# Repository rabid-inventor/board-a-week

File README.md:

# board-a-week
Board a week project. 

Week 1: PASSIVE BLOCK XOR GATE

Attempting to design a pcb to demonstarate an XOR using Discreet silicon and passive components.
REV1 Design Completed 17/07/18

Week 2: TINYMCU

A Breakout for the Atmel/Microchip AtTiny 4/5/9/10 also suitabe for Microchip PIC10F320/322
REV1 Design Complete 24/07/18

Week 3: INTOKICAD / RABIDCHARLIE

First design using KiCAD Wish me luck. This week I ending up with two designs IntoKiCAD is unfinished it was my first steps in using KiCAD. RabidCHARLE is a complete board ready to produce, containing 12 Charlieplexed LEDs.
RabidCHARLIE REV1 Design Complete 31/07/18

Week 4: BUBBLE WATCH

In Progress!!! , base board finish upper board still work to be done 

Week 5: Lets try a new IC

A breakout board for the brand new BMA400 Accelerometer, designed using limited datasheet information. 

Design Complete 27/08/17

Week 6: Blink A Led

Entry for the Mouser / MacroFAB Blink A Led competition

License / Warranty

These source documents are Licenced as CC-BY feel free to use them just drop me a mention in future projects using them. :)
For further details see LICENCE.md

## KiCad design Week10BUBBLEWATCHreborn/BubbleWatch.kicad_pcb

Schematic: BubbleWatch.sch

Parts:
BT1, BT2: Battery_Cell; BatteryHolder_Keystone_3000_1x12mm
C1, C7: 4.7uF; C_0603_1608Metric
C2, C3: 100nF; C_0603_1608Metric
C4: 10nF; C_0603_1608Metric
C5: 1uF; C_0603_1608Metric
C6, C8: 12pF; C_0603_1608Metric
C9: 10uF; C_0603_1608Metric
J1, J2: Conn_02x02_Counter_Clockwise; PinHeader_2x02_P2.54mm_Vertical_SMD
J3: Conn_01x05; Harwin_M20-89005xx_1x05_P2.54mm_Horizontal
L1: 4.7uH; L_Taiyo-Yuden_NR-30xx
R1: 330K; R_0603_1608Metric
R2: 200k; R_0603_1608Metric
R3: 10k; R_0603_1608Metric
RN1, RN2: 220R; R_Array_Concave_4x0402
SW1, SW2, SW3, SW4: SW_Push; Panasonic_EVQPUM_EVQPUD
U1, U2: RedRetroBubbleDisplay; DIP-12_W7.62mm_SMDSocket_SmallPads
U3: STM32F030C8Tx; LQFP-48_7x7mm_P0.5mm
U4: MCP1640BCH; SOT-23-6
Y1: Crystal; Crystal_DS10_D1.0mm_L4.3mm_Horizontal_1EP_style1

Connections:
+3V3: C1.1, C2.1, C3.1, C4.1, C5.1, C9.1, J1.4, J2.4, J3.1, R1.1, R3.1, U3.1, U3.9, U3.24, U3.48, U4.5 (VOUT); also elsewhere on the board
+BATT: BT1.1, BT2.1, C7.1, J1.1, J1.2, J2.1, J2.2, L1.1, U4.3 (EN), U4.6 (VIN)
/BOOT0: U3.44
/BUTTON1: SW1.2, U3.e
/BUTTON2: SW2.2, U3.46
/BUTTON3: SW3.2, U3.45
/BUTTON4: SW4.2, U3.39
/DIS1: U1.1, U3.18
/DIS2: U1.10, U3.19
/DIS3: U1.4, U3.20
/DIS4: U1.6, U3.21
/DIS5: U2.1, U3.25
/DIS6: U2.10, U3.27
/DIS7: U2.4, U3.26
/DIS8: U2.6, U3.28
/I2C1_SCL: J3.3, U3.35
/I2C1_SDA: J3.4, U3.36
/IOSEGA: RN1.4, U3.5
/IOSEGB: RN1.3, U3.6
/IOSEGC: RN1.2, U3.10
/IOSEGD: RN1.1, U3.11
/IOSEGDP: RN2.1, U3.43
/IOSEGE: RN2.4, U3.40
/IOSEGF: RN2.3, U3.41
/IOSEGG: RN2.2, U3.42
/RESET: R3.2, U3.7; also elsewhere on the board
/RTC_XTAL_IN: C6.1, U3.3, Y1.1
/RTC_XTAL_OUT: C8.1, U3.4, Y1.2
/SEGA: RN1.7, U1.12, U2.12
/SEGB: RN1.8, U1.11, U2.11
/SEGC: RN1.6, U1.3, U2.3
/SEGD: RN2.6, U1.8, U2.8
/SEGDP: RN2.8, U1.5, U2.5
/SEGE: RN1.5, U1.2, U2.2
/SEGF: RN2.5, U1.9, U2.9
/SEGG: RN2.7, U1.7, U2.7
/SWDCLK: U3.37; also elsewhere on the board
/SWDIO: U3.34; also elsewhere on the board
GND: BT1.2, BT2.2, C1.2, C2.2, C3.2, C4.2, C5.2, C6.2, C7.2, C8.2, C9.2, J1.3, J2.3, J3.2, J3.5, R2.2, SW1.1, SW2.1, SW3.1, SW4.1, U3.8, U3.23, U3.47, U4.2 (GND); also elsewhere on the board
unnamed: L1.2, U4.1 (SW)
unnamed: R1.2, R2.1, U4.4 (VFB)
unnamed: J3.9, U3.16
unnamed: J3.10, U3.17

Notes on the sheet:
Top/Bottom Board interconnect
Programming header
Decoupleing

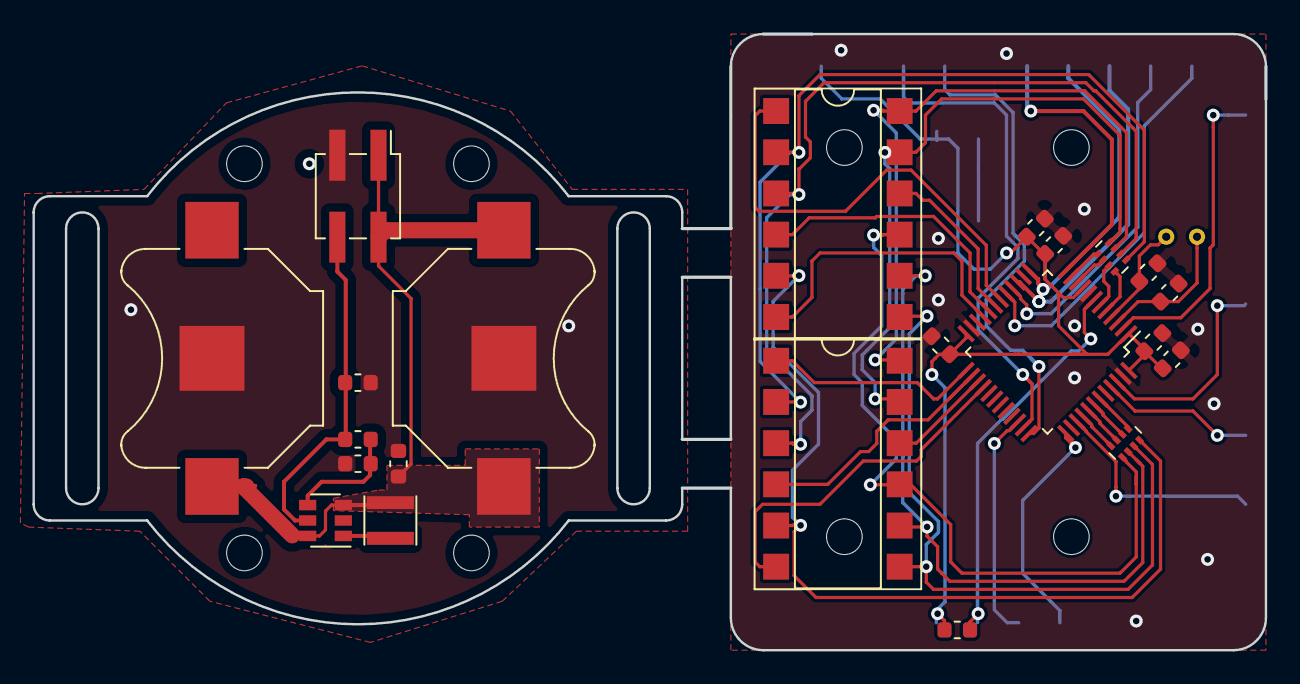
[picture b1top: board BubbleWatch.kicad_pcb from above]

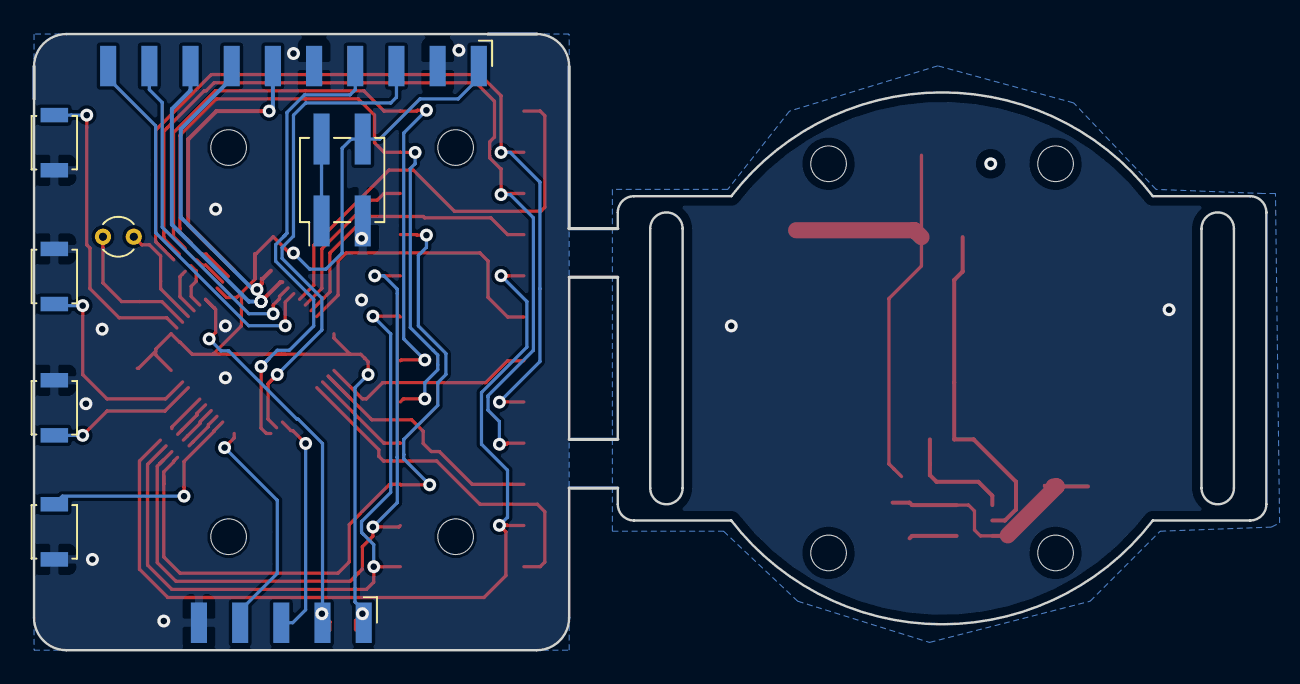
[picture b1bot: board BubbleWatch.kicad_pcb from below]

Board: 2 copper layers, 76.0 x 38.0 mm, 30 parts (8 on the bottom side), 42 nets.

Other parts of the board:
J3#2: Conn_01x05; Harwin_M20-89005xx_1x05_P2.54mm_Horizontal

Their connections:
+3V3: J3#2.1; also elsewhere on the board
/RESET: J3#2.2; also elsewhere on the board
/SWDCLK: J3#2.4; also elsewhere on the board
/SWDIO: J3#2.3; also elsewhere on the board
GND: J3#2.5; also elsewhere on the board

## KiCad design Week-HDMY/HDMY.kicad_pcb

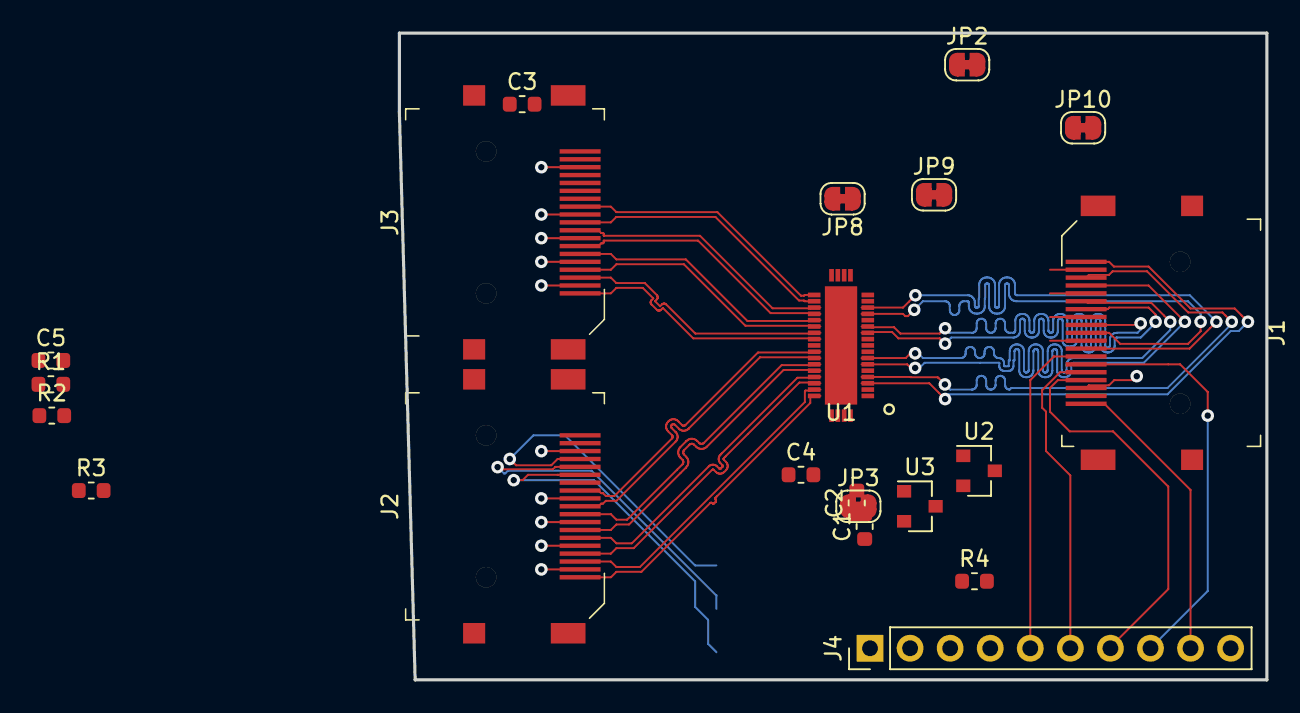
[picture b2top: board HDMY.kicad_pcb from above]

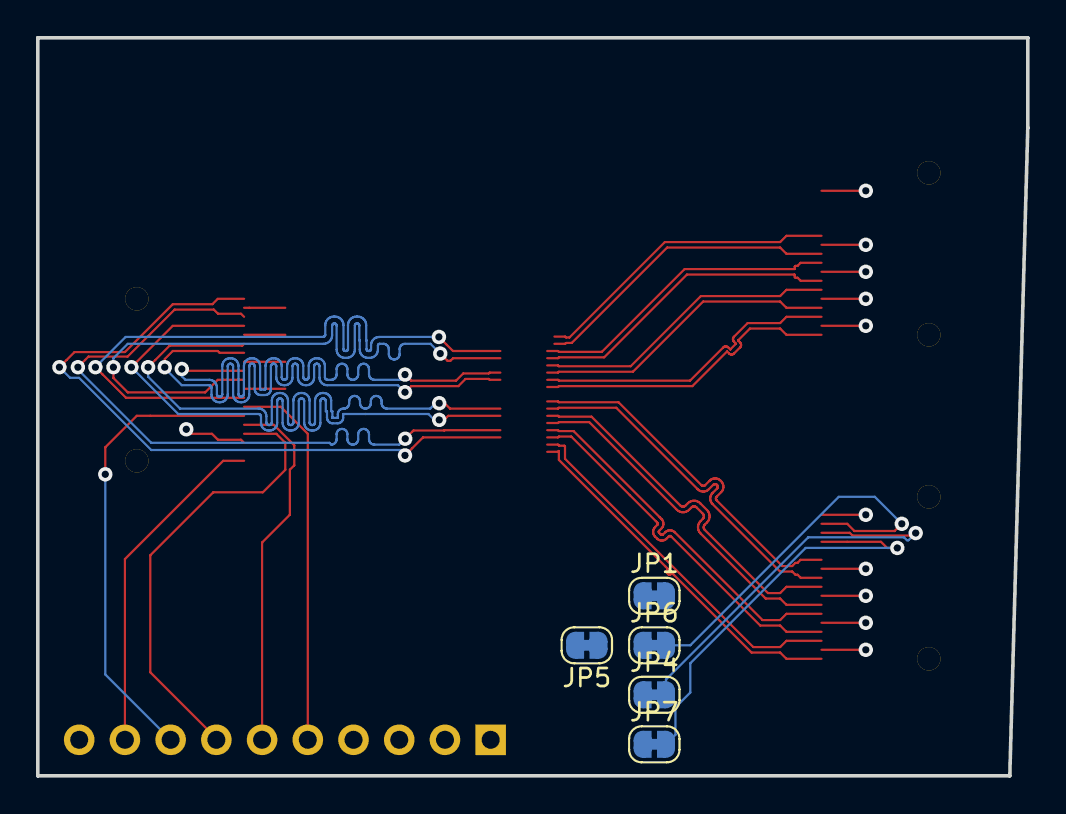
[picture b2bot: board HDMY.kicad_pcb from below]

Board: 2 copper layers, 55.0 x 41.0 mm, 26 parts (5 on the bottom side), 45 nets.

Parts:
C1, C2, C3, C4, C5: 1uF; C_0603_1608Metric
J1, J2, J3: HDMI_A; HDMI_A_Female_2000-1-2-41-00-BK
J4: Conn_01x10; PinHeader_1x10_P2.54mm_Vertical
JP1, JP2, JP3, JP4, JP5, JP6, JP7, JP8, JP9, JP10: SolderJumper_2_Bridged; SolderJumper-2_P1.3mm_Bridged_RoundedPad1.0x1.5mm
R1, R2: 4K7; R_0603_1608Metric
R3: 1K8; R_0603_1608Metric
R4: 1K5; R_0603_1608Metric
U1: TS3DV421; QFN-42-1EP_5x6mm_P0.4mm_EP3.7x4.7mm
U2: AP7333-33SRG-7; SOT-23
U3: AP7333-15SRG-7; SOT-23

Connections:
+1V5: C3.1, C5.1, J4.3, U1.1, U1.5, U1.10, U1.13, U1.17, U1.19, U1.21, U1.39, U1.41, U3.2
+3V3: C2.1, C3.2, C4.1, J4.2, R1.1, R2.1, R3.1, U1.2, U1.8, U1.16, U1.18, U1.20, U1.30, U1.40, U1.42, U2.2, U3.3
+5V: C1.1, J1.18, J2.18, J3.18, J4.1, U2.3
/INACEC: J2.13, JP1.2
/INACLK+: J2.10, U1.32
/INACLK-: J2.12, U1.31
/INAD0+: J2.7, U1.34
/INAD0-: J2.9, U1.33
/INAD1+: J2.4, U1.36
/INAD1-: J2.6, U1.35
/INAD2+: J2.1, U1.38
/INAD2-: J2.3, U1.37
/INAHBD: J2.19, JP9.2
/INASCL: J2.16, JP6.2
/INASDA: J2.15, JP4.2
/INAUTIL: J2.14, JP7.2
/INBCEC: J3.13, JP2.2
/INBCLK+: J3.10, U1.23
/INBCLK-: J3.12, U1.22
/INBD0+: J3.7, U1.25
/INBD0-: J3.9, U1.24
/INBD1+: J3.4, U1.27
/INBD1-: J3.6, U1.26
/INBD2+: J3.1, U1.29
/INBD2-: J3.3, U1.28
/INBHBD: J3.19, JP10.2
/INBSCL: J3.16, JP5.2
/INBSDA: J3.15, JP3.2
/INBUTIL: J3.14, JP8.2
/OUTCEC: J1.13, J4.5, JP1.1, JP2.1
/OUTCLK+: J1.10, U1.14
/OUTCLK-: J1.12, U1.15
/OUTD0+: J1.7, U1.11
/OUTD0-: J1.9, U1.12
/OUTD1+: J1.4, U1.6
/OUTD1-: J1.6, U1.7
/OUTD2+: J1.1, U1.3
/OUTD2-: J1.3, U1.4
/OUTHBD: J1.19, J4.9, JP9.1, JP10.1
/OUTSCL: J1.16, J4.7, JP5.1, JP6.1, R2.2
/OUTSDA: J1.15, J4.6, JP3.1, JP4.1, R1.2
/OUTSEL: J4.4, R4.2
/OUTUTIL: J1.14, J4.8, JP7.1, JP8.1
/SELECT: R3.2, R4.1, U1.9
GND: C1.2, C2.2, C4.2, C5.2, J1.2, J1.5, J1.8, J1.11, J1.17, J1.SH, J2.2, J2.5, J2.8, J2.11, J2.17, J2.SH, J3.2, J3.5, J3.8, J3.11, J3.17, J3.SH, J4.10, U2.1, U3.1

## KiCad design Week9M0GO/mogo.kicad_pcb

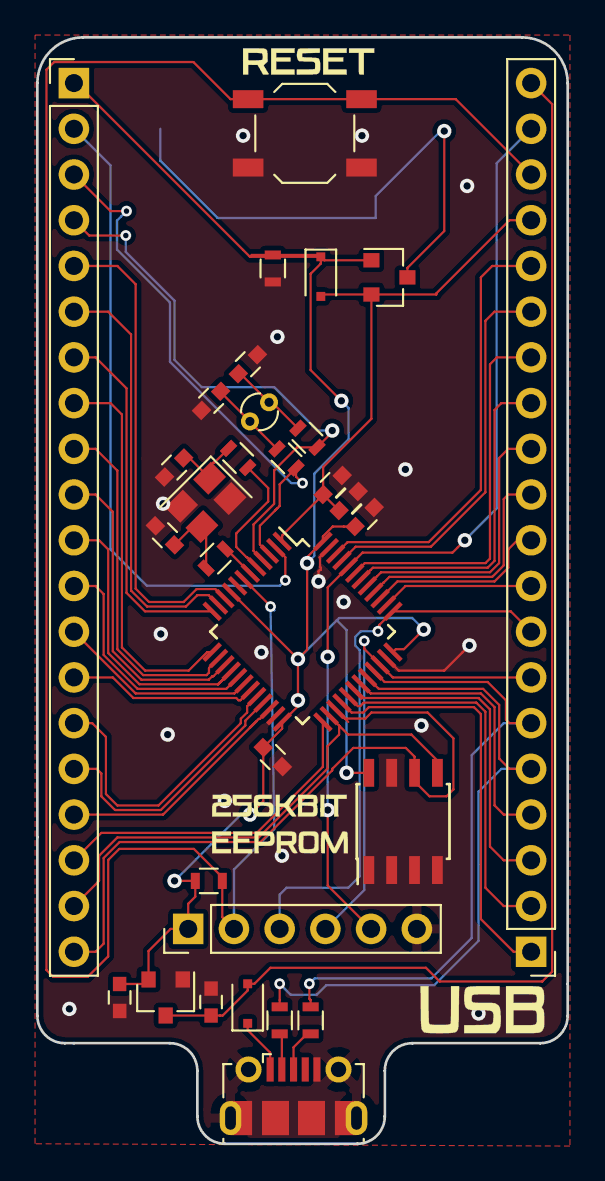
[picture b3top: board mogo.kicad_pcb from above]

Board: 2 copper layers, 29.5 x 61.5 mm, 32 parts (1 on the bottom side), 51 nets.

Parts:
BT1: Battery_Cell; BatteryHolder_Keystone_3000_1x12mm
C1, C2, C3, C4, C5, C6, C7, C8, C9, C10: C; C_0603
D1, D2: DIODE; D_SOD-323F
J1: USB_OTG; USB_Micro-B_Molex-105017-0001
J2: Conn_01x06_Female; PinHeader_1x06_P2.54mm_Vertical
J3, J4: Conn_01x20_Female; Pin_Header_Straight_1x20_Pitch2.54mm
Q1: Q_PMOS_GDS; SOT-23
R1, R2, R3, R4, R5, R6, R7, R8: R; R_0603
SW1: SW_Push; SW_SPST_TL3342
U1: CAT24C256; SOIC-8_3.9x4.9mm_Pitch1.27mm
U2: STM32F072C8Tx; LQFP-48_7x7mm_Pitch0.5mm
U3: AP7333-33SRG-7; SOT-23
Y1: Crystal_GND24; Crystal_SMD_SeikoEpson_FA238-4Pin_3.2x2.5mm
Y2: Crystal 32.76 Khz; Crystal_Round_d1.0mm_Vertical

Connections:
+3V3: C8.1, C9.1, C10.1, D2.1, J2.1, J4.1, Q1.1, R7.1, R8.1, U1.8, U2.9, U2.24, U2.36, U2.48, U3.2
+BATT: C5.1, C6.1, D2.2, J3.17, Q1.2, U2.1
/BOOT0: J2.5, J3.19, U2.44
/OSC_IN: R1.1, U2.5
/OSC_OUT: R2.1, U2.6
/PA0: J4.5, U2.10
/PA1: J4.6, U2.11
/PA2: J4.7, U2.12
/PA3: J4.8, U2.13
/PA4: J4.9, U2.14
/PA5: J4.10, U2.15
/PA6: J4.11, U2.16
/PA7: J4.12, U2.17
/PA8: J3.2, U2.29
/PA9: J3.3, U2.30
/PA10: J3.4, U2.31
/PA15: J3.9, U2.38
/PB0: J4.13, U2.18
/PB1: J4.14, U2.19
/PB2: J4.15, U2.20
/PB3: J3.10, U2.39
/PB4: J3.11, U2.40
/PB5: J3.12, U2.41
/PB6: J3.13, U2.42
/PB7: J3.14, U2.43
/PB8: J3.15, U2.45
/PB9: J3.16, U2.46
/PB10: J4.16, U2.21
/PB11: J4.17, U2.22
/PB12: J4.18, U2.25
/PB13: J4.19, U1.5, U2.26
/PB14: J4.20, U1.6, U2.27
/PB15: J3.1, U2.28
/PC13: J4.2, U2.2
/RTC_OSC_IN: J4.3, R5.1, U2.3
/RTC_OSC_OUT: J4.4, R6.1, U2.4
/SWCLK: J2.3, J3.8, U2.37
/SWDIO: J2.4, J3.7, U2.34
/USB_D+: J3.6, R3.1, U2.33
/USB_D-: J3.5, R4.1, U2.32
/_RESET: J2.2, J3.18, R7.2, SW1.2, U2.7
GND: BT1.2, C1.2, C2.2, C3.2, C4.2, C5.2, C6.2, C7.2, C8.2, C9.2, C10.2, J1.5, J1.6, J2.6, R8.2, SW1.1, U1.1, U1.2, U1.3, U1.4, U1.7, U2.23, U2.35, U2.47, U3.1, Y1.2, Y1.4
unnamed: BT1.1, Q1.3
unnamed: C1.1, R1.2, Y1.1
unnamed: C2.1, R2.2, Y1.3
unnamed: C3.1, R5.2, Y2.1
unnamed: C4.1, R6.2, Y2.2
unnamed: D1.1, J1.1
unnamed: J1.2, R4.2
unnamed: J1.3, R3.2
VBUS: C7.1, D1.2, J3.20, U3.3

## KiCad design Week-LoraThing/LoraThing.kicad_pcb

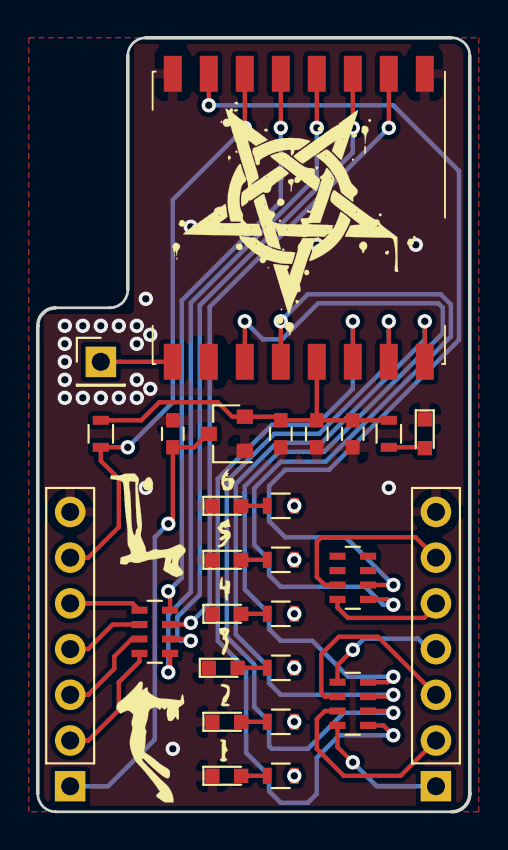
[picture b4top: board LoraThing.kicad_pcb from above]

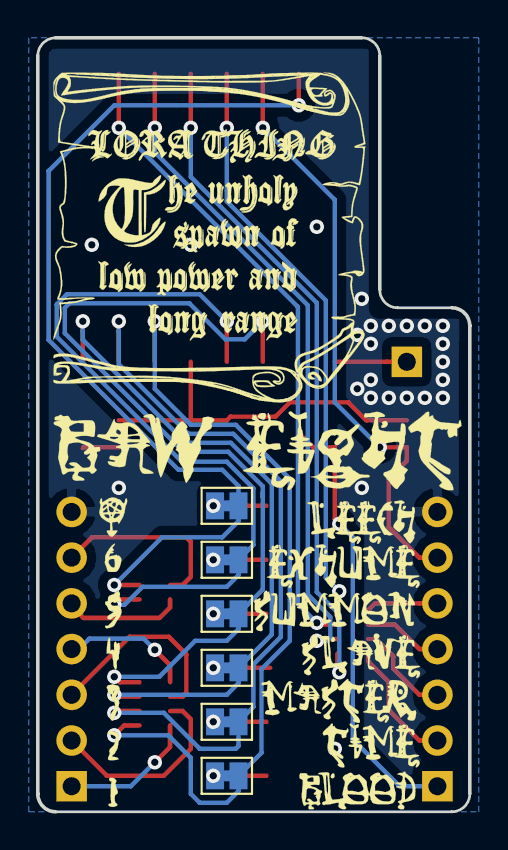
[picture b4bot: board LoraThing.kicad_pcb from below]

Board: 2 copper layers, 24.0 x 43.0 mm, 33 parts (6 on the bottom side), 38 nets.

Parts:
C1, C2, C4: 1uF; C_0603
C3: 100nF; C_0603
D1, D2, D3, D4, D5, D6, D7: LED; LED_0603
J1, J2: Conn_01x07_Male; Pin_Header_Straight_1x07_Pitch2.54mm
J3: Conn_01x01_Female; Pin_Header_Straight_1x01_Pitch2.54mm
JP1, JP2, JP4, JP5, JP6: Jumper_NC_Small; SolderJumper-2_P1.3mm_Bridged_Pad1.0x1.5mm
R1, R2, R3, R4, R5, R6, R7: 330R; R_0603
R8: 10K; R_0603
RN1, RN2, RN3: 100R; R_Array_Concave_4x0603
U1: AP7333-33SRG-7; SOT-23
U2: RFM95W-868S2; Hopref_RFM9XW_SMD
eJP3: Jumper_NC_Small; SolderJumper-2_P1.3mm_Bridged_Pad1.0x1.5mm

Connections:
+3V3: C2.1, C3.1, C4.1, R7.2, R8.2, U1.2, U2.13
/ANTENNA: J3.1, U2.9
/EXT_GPIO1: J2.1, RN2.8
/EXT_GPIO2: J2.2, RN2.7
/EXT_GPIO3: J2.3, RN2.6
/EXT_GPIO4: J2.4, RN2.5
/EXT_GPIO5: J2.5, RN3.8
/EXT_GPIO6: J2.6, RN3.7
/GPIO1: JP1.1, RN2.1, U2.14
/GPIO2: JP2.1, RN2.2, U2.15
/GPIO3: RN2.3, U2.16, eJP3.1
/GPIO4: JP4.1, RN2.4, U2.11
/GPIO5: JP5.1, RN3.1, U2.12
/GPIO6: JP6.1, RN3.2, U2.7
/RESET: J1.6, R8.1, U2.6
/SPI_CS: RN1.4, U2.5
/SPI_EXT_CS: J1.5, RN1.5
/SPI_EXT_MISO: J1.4, RN1.6
/SPI_EXT_MOSI: J1.3, RN1.7
/SPI_EXT_SCK: J1.2, RN1.8
/SPI_MISO: RN1.3, U2.2
/SPI_MOSI: RN1.2, U2.3
/SPI_SCK: RN1.1, U2.4
GND: C1.2, C2.2, C3.2, C4.2, D1.1, D2.1, D3.1, D4.1, D5.1, D6.1, D7.1, J1.7, J2.7, U1.1, U2.1, U2.8, U2.10
unnamed: D1.2, R1.1
unnamed: D2.2, R2.1
unnamed: D3.2, R3.1
unnamed: D4.2, R4.1
unnamed: D5.2, R5.1
unnamed: D6.2, R6.1
unnamed: D7.2, R7.1
unnamed: JP1.2, R1.2
unnamed: JP2.2, R2.2
unnamed: R3.2, eJP3.2
unnamed: JP4.2, R4.2
unnamed: JP5.2, R5.2
unnamed: JP6.2, R6.2
VCC: C1.1, J1.1, U1.3

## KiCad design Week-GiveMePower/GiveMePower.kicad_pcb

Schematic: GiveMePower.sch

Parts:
C1, C2: C; C_1210
C3, C4: C; C_0603
D1: LED; LED_0603
J1, J2, J3, J4: Conn_01x02_Male; Pin_Header_Straight_1x02_Pitch2.54mm
J5, J6, J7: Conn_01x02_Female; Pin_Header_Straight_1x02_Pitch2.54mm
J8, J9, J10: Screw_Terminal_01x02; TerminalBlock_Phoenix_PT-3.5mm_2pol
J11, J12, J13: Conn_01x01_Female; MountingHole_6mm_Pad_Via
L2: L; L_Taiyo-Yuden_MD-3030
R1: R; R_0603
TP1, TP2, TP3: TestPoint_Probe; Measurement_Point_Square-SMD-Pad_Big
U1: AP1117-33; SOT-223-3_TabPin2

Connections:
/AUXIn: J7.1, J10.1
/AUXout: J7.2, J10.2
/EarthGND: J12.1
/EarthGround: J1.1
/LowPassIn: C3.1, J2.2, L2.1
/LowPassOut: C2.1, J4.1, L2.2
/Output3V3: C4.1, J6.1, J9.1, TP2.1, U1.2 (VO)
/OutputVCC: J3.2, J4.2, J5.1, J8.1, TP1.1
GND: C1.2, C2.2, C3.2, C4.2, D1.1, J1.2, J5.2, J6.2, J8.2, J9.2, J13.1, TP3.1, U1.1 (GND)
unnamed: D1.2, R1.2
VCC: C1.1, J2.1, J3.1, J11.1, R1.1, U1.3 (VI)

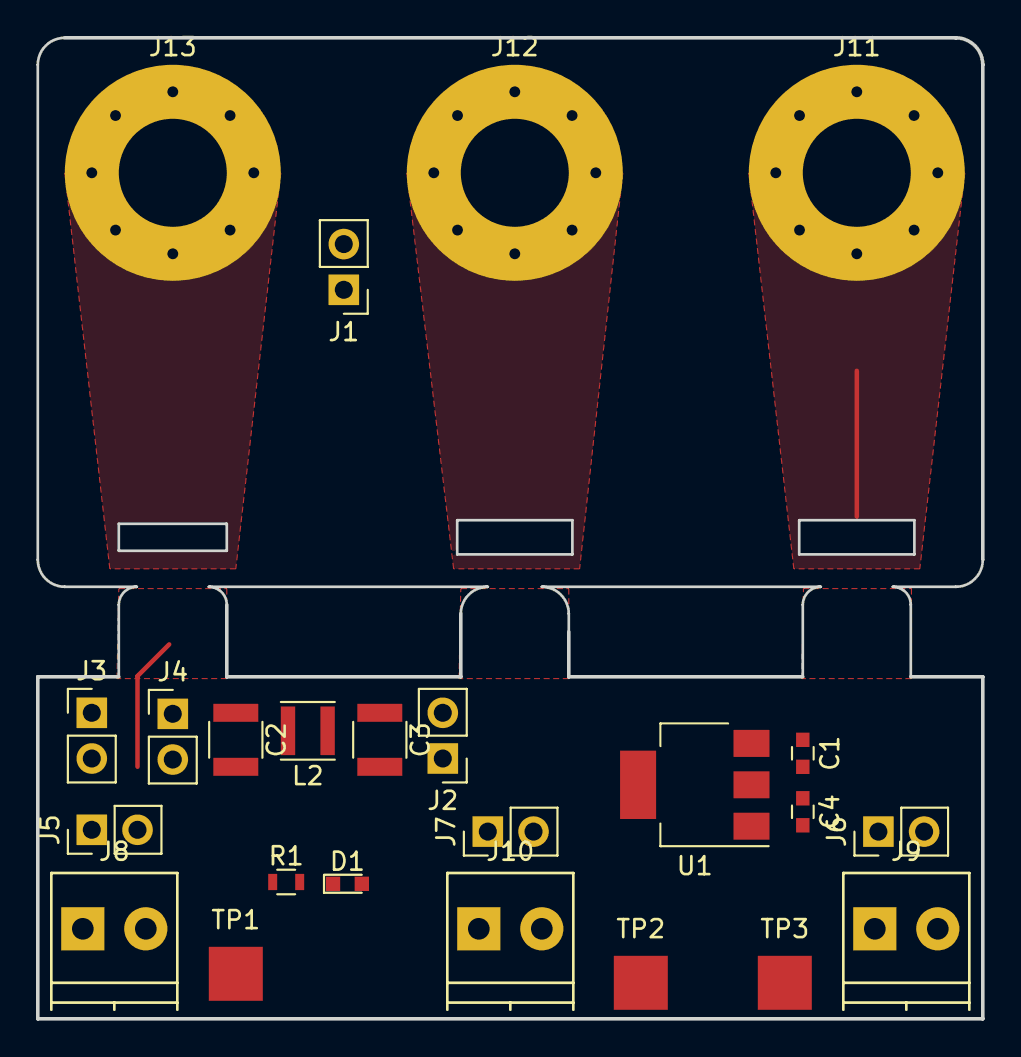
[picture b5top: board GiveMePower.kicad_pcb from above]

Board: 2 copper layers, 52.5 x 54.5 mm, 24 parts (0 on the bottom side), 9 nets.

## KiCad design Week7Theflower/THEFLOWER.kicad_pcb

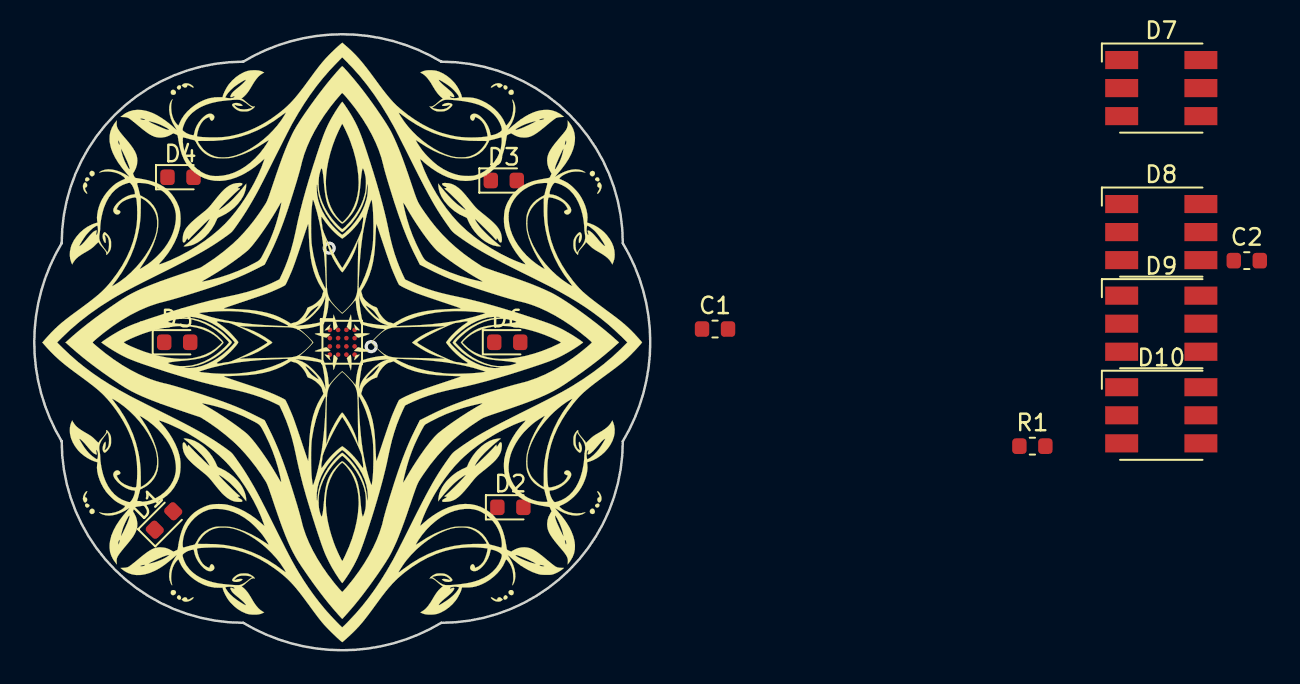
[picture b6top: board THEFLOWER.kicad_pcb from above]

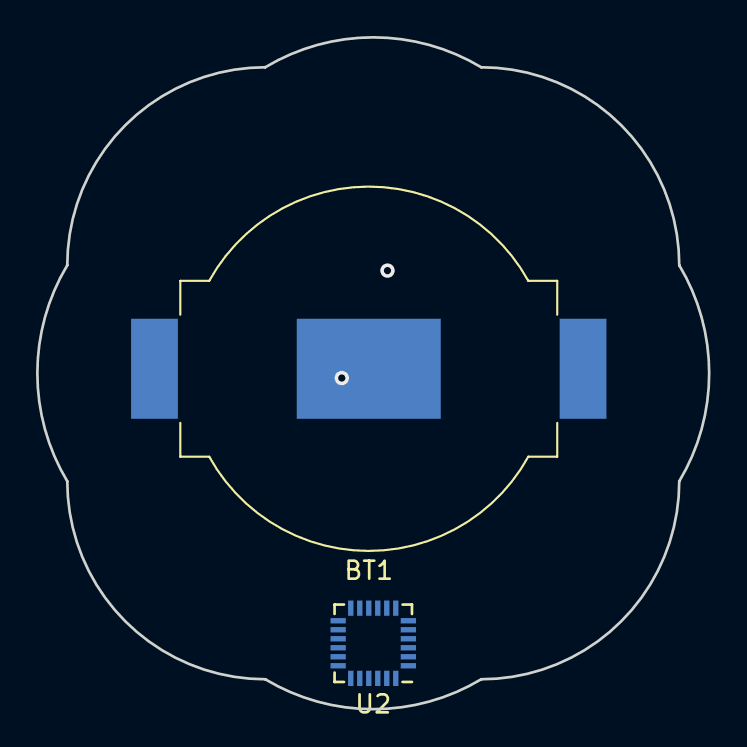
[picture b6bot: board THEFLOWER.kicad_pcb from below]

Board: 2 copper layers, 37.3 x 37.3 mm, 16 parts (2 on the bottom side), 21 nets, no tracks yet.

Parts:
BT1: Battery_Cell; BatteryHolder_MPD_BC2003_1x2032
C1: 1uF; C_0603_1608Metric
C2: 100nF; C_0603_1608Metric
D1, D2, D3, D4, D5, D6: LED; LED_0603_1608Metric
D7, D8, D9, D10: LED_RGB; LED_RGB_5050-6
R1: 3k3; R_0603_1608Metric
U1: LPC1104UK; WLCSP-16_4x4_B2.17x2.32mm_P0.5mm
U2: SN3218; QFN-24_4x4mm_P0.5mm

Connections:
+3V3: C1.1, C2.2, D1.2, D2.2, D3.2, D4.2, D5.2, D6.2, D7.4, D7.5, D7.6, D8.4, D8.5, D8.6, D9.4, D9.5, D9.6, D10.4, D10.5, D10.6, U2.3
/BACKLED1: D5.1, U2.11
/BACKLED2: D6.1, U2.16
/C1B: D7.3, U2.10
/C1G: D7.2, U2.9
/C1R: D7.1, U2.8
/C2B: D8.3, U2.15
/C2G: D8.2, U2.14
/C2R: D8.1, U2.13
/C3B: D9.3, U2.20
/C3G: D9.2, U2.19
/C3R: D9.1, U2.18
/C4B: D10.2, U2.1
/C4G: D10.3, U2.23
/C4R: D10.1, U2.22
/LEAF1: D1.1, U2.7
/LEAF2: D2.1, U2.12
/LEAF3: D3.1, U2.17
/LEAF4: D4.1, U2.21
GND: C1.2, C2.1, R1.2, U2.4
unnamed: R1.1, U2.2

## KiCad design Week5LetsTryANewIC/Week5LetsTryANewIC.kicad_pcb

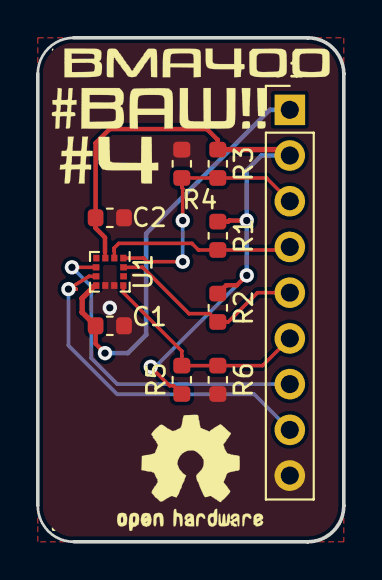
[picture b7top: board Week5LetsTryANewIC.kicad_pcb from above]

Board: 2 copper layers, 17.0 x 28.0 mm, 10 parts (0 on the bottom side), 9 nets.

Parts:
C1, C2: 100nF; C_0603_1608Metric
J1: Conn_01x09_Male; PinHeader_1x09_P2.54mm_Vertical
R1, R2, R3, R4, R5, R6: 4K7; C_0603_1608Metric
U1: BMA400; LGA-12_2x2mm_P0.5mm

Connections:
/CSB: J1.6, R5.2, R6.1, U1.10
/INT1: J1.7, U1.5
/INT2: J1.8, U1.6
/SCX: J1.5, R2.2, U1.12
/SDA: J1.3, R3.2, R4.1, U1.1
/SDX: J1.4, R1.2, U1.2
GND: C1.2, C2.2, J1.9, R4.2, R6.2, U1.8, U1.9
VDD: C1.1, J1.1, U1.7
VDDA: C2.1, J1.2, R1.1, R2.1, R3.1, R5.1, U1.3

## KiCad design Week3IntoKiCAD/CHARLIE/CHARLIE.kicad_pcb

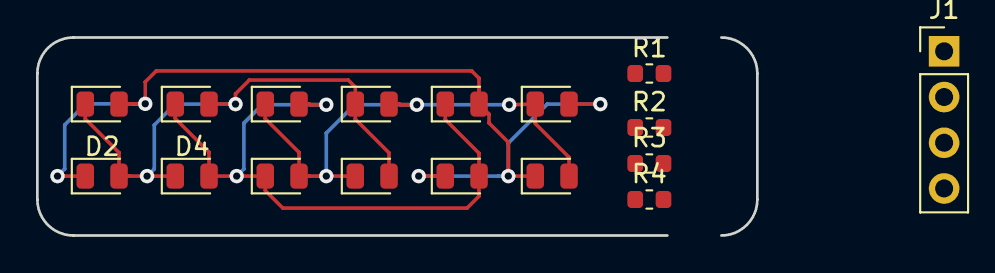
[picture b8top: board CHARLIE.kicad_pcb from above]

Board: 2 copper layers, 40.0 x 11.0 mm, 17 parts (0 on the bottom side), 8 nets.

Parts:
D1, D2, D3, D4, D5, D6, D7, D8, D9, D10, D11, D12: LED; LED_0805_2012Metric
J1: Conn_01x04_Male; PinHeader_1x04_P2.54mm_Vertical
R1, R2, R3, R4: R; R_0603_1608Metric

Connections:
/IO1: D1.2, D2.1, D9.2, D10.1, D11.2, D12.1, R1.2
/IO2: D1.1, D2.2, D3.2, D4.1, D7.1, D8.2, R2.2
/IO3: D3.1, D4.2, D5.2, D6.1, D9.1, D10.2, R3.2
/IO4: D5.1, D6.2, D7.2, D8.1, D11.1, D12.2, R4.2
/PINCON1: J1.1, R1.1
/PINCON2: J1.2, R2.1
/PINCON3: J1.3, R3.1
/PINCON4: J1.4, R4.1

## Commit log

2018-07-09 Board schmatic complete
    Finished board schematic. started to layout components.
2018-07-10 First routing Started
2018-07-11 More routing and schmatic fixes
2018-07-12 More routing Tweaking and started to make pretty
2018-07-15 Completed ERC and more desgin tweeks
    Completed ERC making sure i have vaules for parts. Changed header through holds to help with distace to the board edge.
2018-07-16 Routing finished
2018-07-17 Rev1 Finished
    DRC finished silk and artwork added documented fonts used
2018-07-17 added rendered images and updated readme
2018-07-17 Started week2s board
2018-07-18 Started Week 2 ATTINY4/5/9/10
    added parts library to support boards
2018-07-19 schemematic updates
2018-07-20 started processing gerber for week1 more schmatic work for week 2
2018-07-21 Week2 schmatics finished started Week3
2018-07-22 week 2 routing cleaned started silk
2018-07-23 Little bit of playing with the silk for week2(unfinished)
2018-07-24 Week2 Schmatic finished
    Week2 Schmatic finished and tidied up ERC check done values and labels added, added CC-BY Licence details and readme updated
2018-07-24 week 2 more silkwork
2018-07-24 Week2 PCB Complete
2018-07-24 updated readme and renamed week 2 dirctory
2018-07-25 Started Week4
2018-07-28 Restarted Week 3
    Needed to start a new simpler board for week 3 after understanding more about KiCAD.
2018-07-29 Week 3 charlie routing underway
2018-07-30 sorting uncommited changes
2018-07-30 Week3 route finished slik started
2018-07-30 Had forgot to save OPPPs resync
2018-07-30 Week 3 Complete
2018-07-31 Started the flower
2018-07-31 Update to base pattern
2018-08-01 Updated README and tidied the directories
2018-08-01 Started week 4 schmatic
2018-08-03 more bubble watch schematic work
2018-08-05 Schematic done datasheet added
2018-08-05 schematic complete week 4
2018-08-05 Update .gitignore
    Kicad project did no sync removed *.pro
2018-08-05 recommited to update project files for kicad
2018-08-05 Started layout week 4
2018-08-06 update all pro files
2018-08-06 more layout work for Week 4
2018-08-07 more routing work
2018-08-08 new board ideas
2018-08-11 More work on week 4
    Converting display placements to SMT to allow mor room on board.
2018-08-12 more week 4 board work
    full rearangement of pcb an re routing
2018-08-12 repush schmatic
2018-08-13 more week4 routeing reformated dispaly agiain
2018-08-14 end of day commit
2018-08-26 week 5 schematic complete
    added week5 progress
2018-08-26 week 5 routing complete
    silk and artwork still required
2018-08-27 tidying up older projects
2018-08-27 moreschematic work
2018-08-27 finished board updated readme
2018-08-28 Started Week 6
    Started week 6 for Mousers Blink An LED
2018-08-29 Added gerbers to week 5
2018-08-29 End of day sync
2018-09-16 started schematic work on week 7
2018-09-16 trying to make component choices work
2018-09-18 more work on flower
2018-09-24 started on give me power
2018-09-26 more work on week 7
2018-09-27 flower updates
2018-09-28 give me power update
2018-10-08 Finish layout Give Me Power
2018-10-08 updated project file
2018-10-09 started M0GO
2018-10-09 More schematic work
2018-10-12 Added Lora Thing schmatic and almost finished board
2018-10-14 syncing work from lora thing
2018-10-14 loraThing routing complete artwork started
2018-10-14 Resyn forgot to save first (again)
2018-10-15 loar thing artworkupdated
2018-10-16 lorathing artwork
2018-10-16 lora thing complete
2018-10-16 re arrange directories
2018-10-17 m0go SCHEMATIC WORK
2018-11-01 finish schmatic m0go
2018-11-01 resync
2018-11-10 lib updates
2018-11-29 started routing
2018-12-06 board work m0go
2018-12-10 mogo routing finished
2018-12-11 routign finisted on M0GO
2018-12-13 grebers created mogo finished
2018-12-13 revisiting the bubble watch from week 4
2019-01-02 Bubblewathc reborn routing finished
2019-01-02 end of day push
2019-01-03 Started HDMY hdmi swticher
2019-01-03 almost completed HDMY schematic
2019-01-06 completed schmatic working on layout for HDMY
2019-02-26 added rain Randon Air Indication Node
2019-02-27 Rain silks and gerber done
2019-02-28 differential traces done on hdmy
2019-03-01 end of week push
2019-03-18 started first pcbmode project
